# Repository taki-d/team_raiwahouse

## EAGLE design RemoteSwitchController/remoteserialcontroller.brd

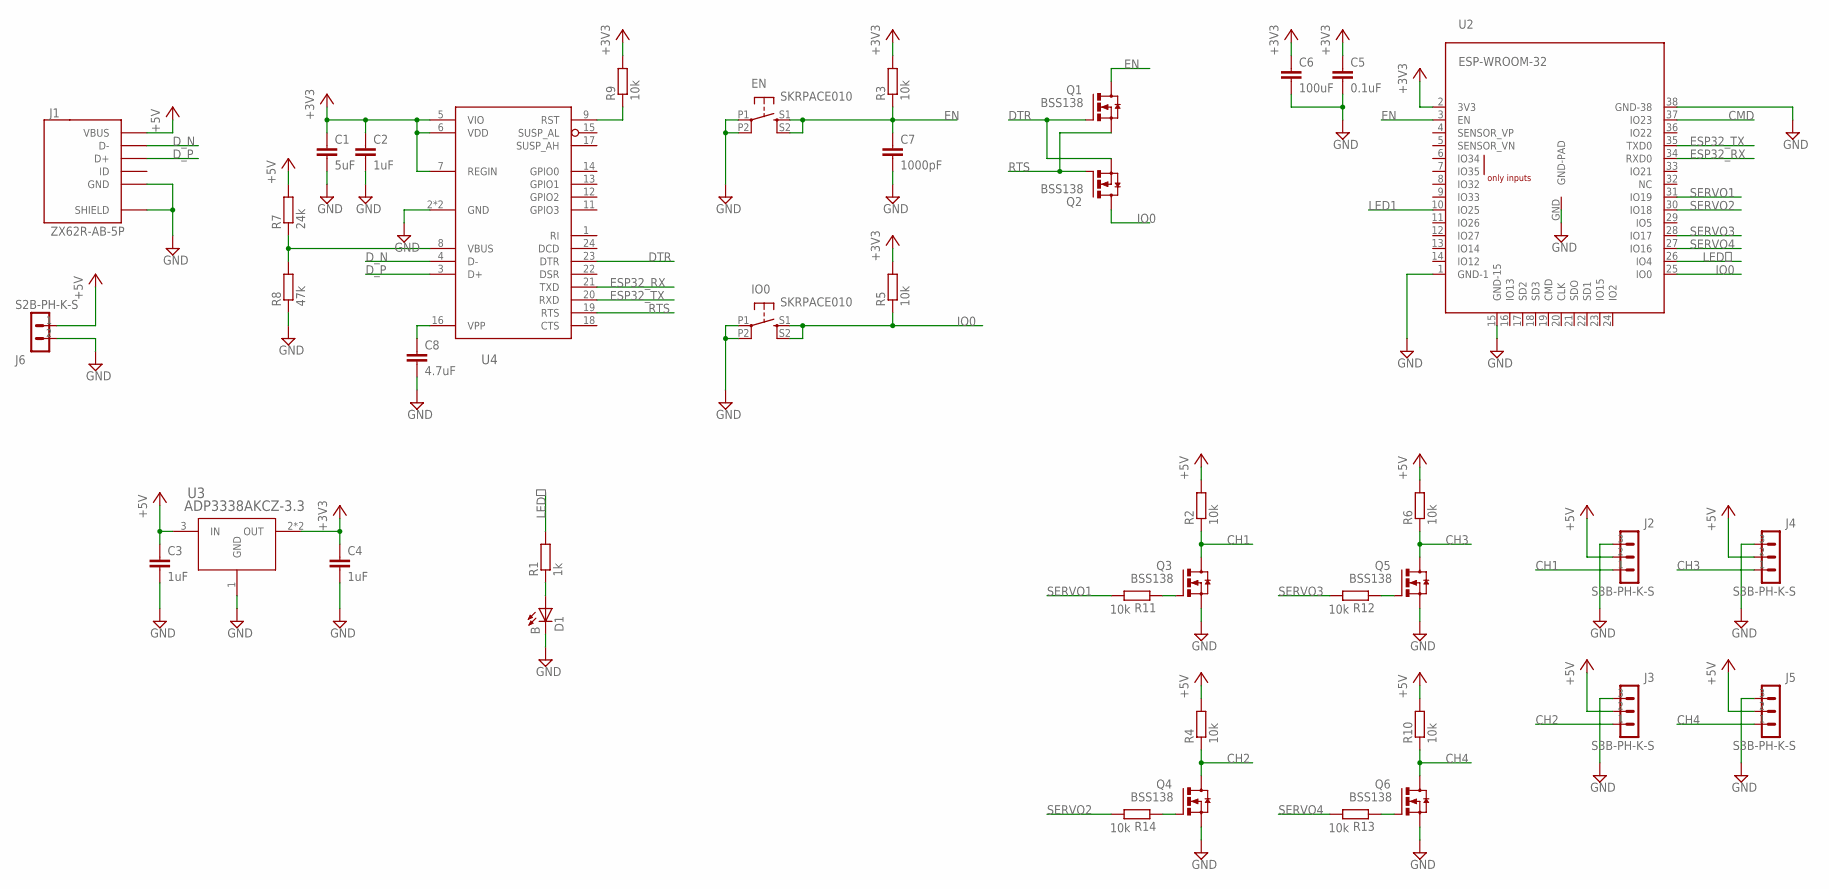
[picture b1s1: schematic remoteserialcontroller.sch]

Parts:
C1: 5uF; C0603
C2, C3, C4: 1uF; C0603
C5: 0.1uF; C0603
C6: 100uF; C1210
C7: 1000pF; C0603
C8: 4.7uF; C0603
D1: B; CHIPLED_0603
EN: SKRPACE010
IO0: SKRPACE010
J1: ZX62R-AB-5P; ZX62R-B-5PA
J2, J3, J4, J5: S3B-PH-K-S
J6: S2B-PH-K-S
Q1, Q2, Q3, Q4, Q5, Q6: BSS138; SOT23-N-MOSFET
R1: 1k; R0603
R2, R3, R4, R5, R6, R9, R10, R11, R12, R13, R14: 10k; R0603
R7: 24k; R0603
R8: 47k; R0603
U2: ESP-WROOM-32
U3: ADP3338AKCZ-3.3; SOT233
U4: CP2104; QFN24-SILABS

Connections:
+3V3: C1.1, C2.1, C4.1, C5.1, C6.1, R3.2, R5.2, R9.2, U2.2 (3V3), U3.2 (OUT), U3.4 (OUT), U4.5 (VIO), U4.6 (VDD), U4.7 (REGIN)
+5V: C3.1, J1.VCC (VBUS), J2.2, J3.2, J4.2, J5.2, J6.1, R2.2, R4.2, R6.2, R7.2, R10.2, U3.3 (IN)
CH1: J2.1, Q3.D, R2.1
CH2: J3.1, Q4.D, R4.1
CH3: J4.1, Q5.D, R6.1
CH4: J5.1, Q6.D, R10.1
CMD: U2.37 (IO23)
DTR: Q1.G, Q2.S, U4.23 (DTR)
D_N: J1.D-, U4.4 (D-)
D_P: J1.D+, U4.3 (D+)
EN: C7.1, EN.S1 (S), EN.S2 (S1), Q1.D, R3.1, U2.3 (EN)
ESP32_RX: U2.34 (RXD0), U4.21 (TXD)
ESP32_TX: U2.35 (TXD0), U4.20 (RXD)
GND: C1.2, C2.2, C3.2, C4.2, C5.2, C6.2, C7.2, C8.2, D1.C, EN.P1, EN.P2 (P1), IO0.P1, IO0.P2 (P1), J1.GND, J1.SHIELD@1 (SHIELD), J1.SHIELD@2 (SHIELD), J1.SHIELD@3 (SHIELD), J1.SHIELD@4 (SHIELD), J2.3, J3.3, J4.3, J5.3, J6.2, Q3.S, Q4.S, Q5.S, Q6.S, R8.1, U2.1 (GND-1), U2.15 (GND-15), U2.38 (GND-38), U2.GND (GND-PAD), U3.1 (GND), U4.2 (GND), U4.25 (GND)
IO0: IO0.S1 (S), IO0.S2 (S1), Q2.D, R5.1, U2.25 (IO0)
LED1: U2.10 (IO25)
LED１: R1.2, U2.26 (IO4)
unnamed: Q3.G, R11.1
unnamed: Q5.G, R12.1
unnamed: Q6.G, R13.1
unnamed: Q4.G, R14.1
unnamed: R9.1, U4.9 (RST)
unnamed: R7.1, R8.2, U4.8 (VBUS)
unnamed: C8.1, U4.16 (VPP)
unnamed: D1.A, R1.1
RTS: Q1.S, Q2.G, U4.19 (RTS)
SERVO1: R11.2, U2.31 (IO19)
SERVO2: R14.2, U2.30 (IO18)
SERVO3: R12.2, U2.28 (IO17)
SERVO4: R13.2, U2.27 (IO16)

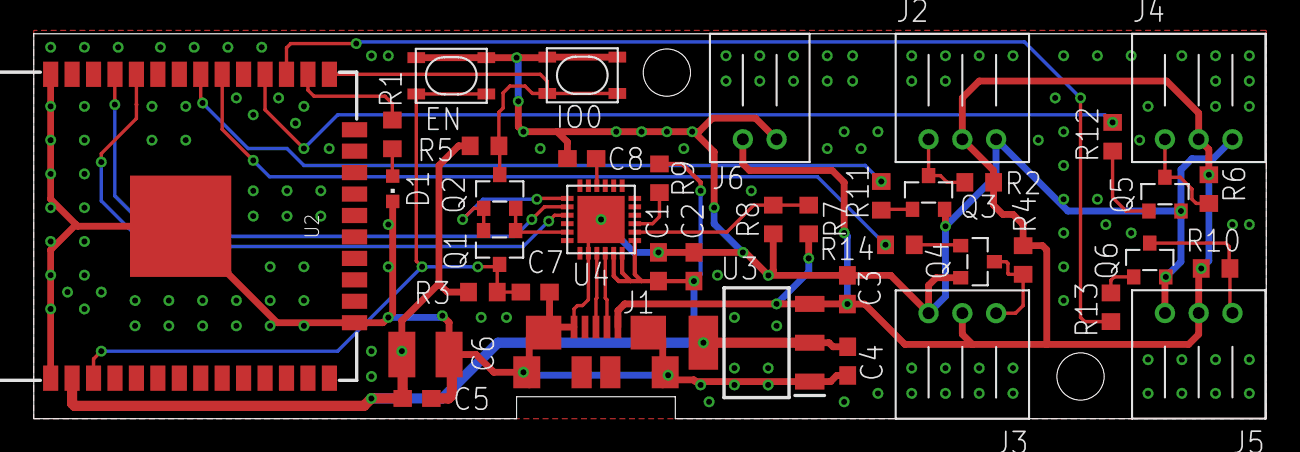
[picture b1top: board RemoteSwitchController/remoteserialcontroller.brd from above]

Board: 2 copper layers, 73.0 x 22.8 mm, 40 parts (0 on the bottom side), 28 nets.

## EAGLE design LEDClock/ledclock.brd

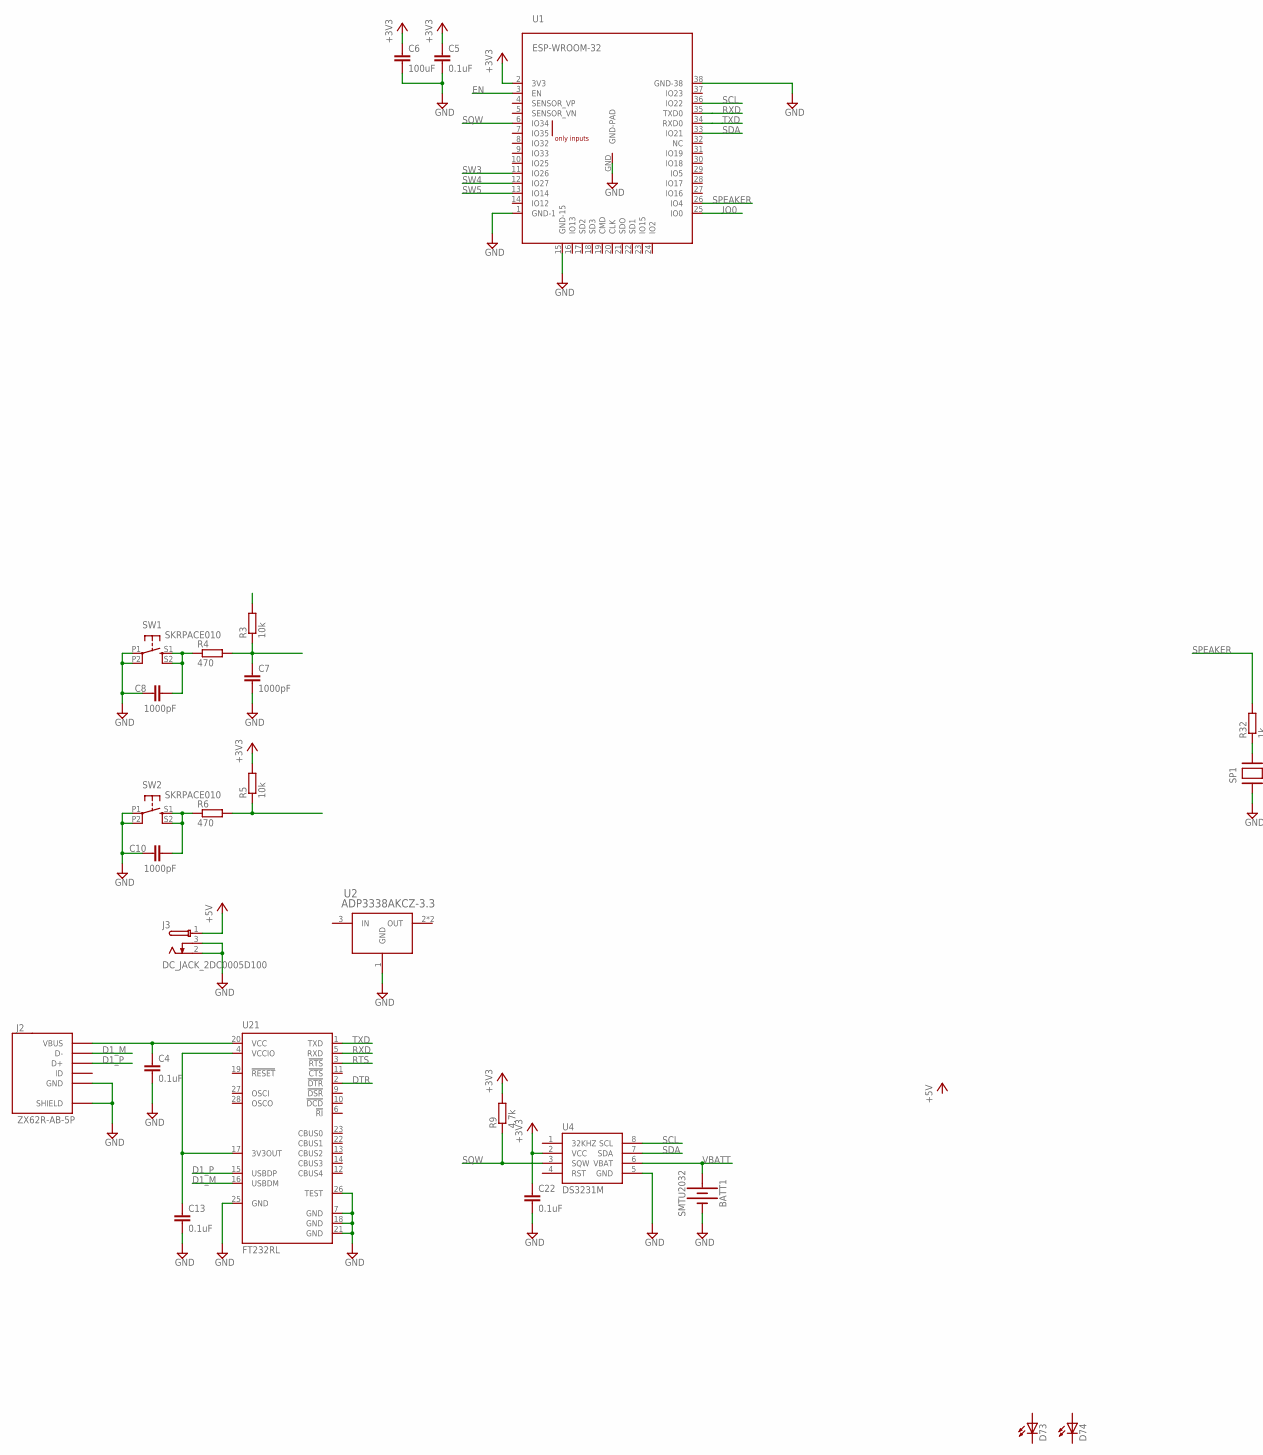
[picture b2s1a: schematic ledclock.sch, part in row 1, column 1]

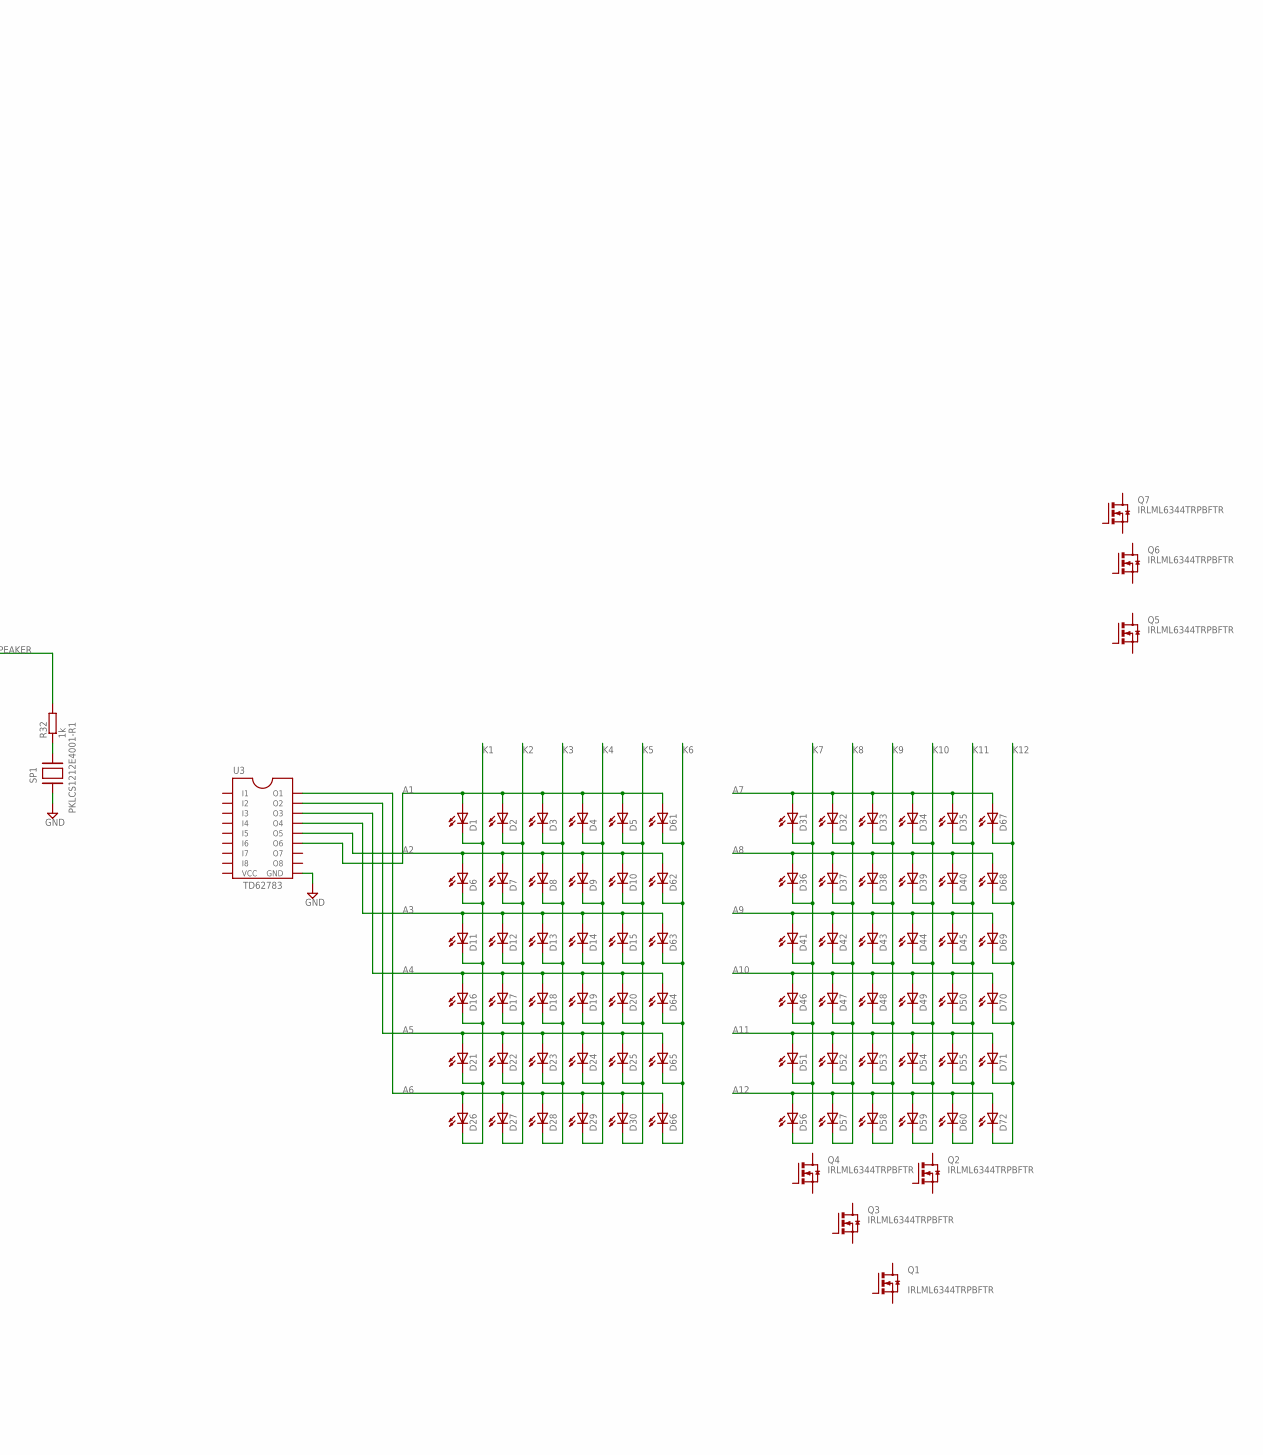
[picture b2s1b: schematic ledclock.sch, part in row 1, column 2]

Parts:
BATT1: SMTU2032
C4, C5, C13, C22: 0.1uF; C0603
C6: 100uF; C1210
C7, C8, C10: 1000pF; C0603
D1, D2, D3, D4, D5, D6, D7, D8, D9, D10, D11, D12, D13, D14, D15, D16, D17, D18, D19, D20, D21, D22, D23, D24, D25, D26, D27, D28, D29, D30, D31, D32, D33, D34, D35, D36, D37, D38, D39, D40, D41, D42, D43, D44, D45, D46, D47, D48, D49, D50, D51, D52, D53, D54, D55, D56, D57, D58, D59, D60, D61, D62, D63, D64, D65, D66, D67, D68, D69, D70, D71, D72, D73, D74: LED-H-0603; CHIPLED_0603-H
J2: ZX62R-AB-5P; ZX62R-B-5PA
J3: DC_JACK_2DC0005D100
Q1, Q2, Q3, Q4, Q5, Q6, Q7: IRLML6344TRPBFTR; SOT23-N-MOSFET
R3, R5: 10k; R0603
R4, R6: 470; R0603
R9: 4.7k; R0603
R32: 1k; R0603
SP1: PKLCS1212E4001-R1
SW1, SW2: SKRPACE010
U1: ESP-WROOM-32
U2: ADP3338AKCZ-3.3; SOT233
U3: TD62783; SOP18_TOSHIBA
U4: DS3231M; SO08
U21: FT232RL; SSOP28

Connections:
+3V3: C5.1, C6.1, C22.1, R3.2, R5.2, R9.2, U1.2 (3V3), U4.2 (VCC)
+5V: J3.1
A1: D1.A, D2.A, D3.A, D4.A, D5.A, D61.A, U3.13 (O6)
A2: D6.A, D7.A, D8.A, D9.A, D10.A, D62.A, U3.14 (O5)
A3: D11.A, D12.A, D13.A, D14.A, D15.A, D63.A, U3.15 (O4)
A4: D16.A, D17.A, D18.A, D19.A, D20.A, D64.A, U3.16 (O3)
A5: D21.A, D22.A, D23.A, D24.A, D25.A, D65.A, U3.17 (O2)
A6: D26.A, D27.A, D28.A, D29.A, D30.A, D66.A, U3.18 (O1)
A7: D31.A, D32.A, D33.A, D34.A, D35.A, D67.A
A8: D36.A, D37.A, D38.A, D39.A, D40.A, D68.A
A9: D41.A, D42.A, D43.A, D44.A, D45.A, D69.A
A10: D46.A, D47.A, D48.A, D49.A, D50.A, D70.A
A11: D51.A, D52.A, D53.A, D54.A, D55.A, D71.A
A12: D56.A, D57.A, D58.A, D59.A, D60.A, D72.A
D1_M: J2.D-, U21.16 (USBDM)
D1_P: J2.D+, U21.15 (USBDP)
DTR: U21.2 (!DTR)
EN: C7.1, R3.1, R4.2, U1.3 (EN)
GND: BATT1.N (-), C4.2, C5.2, C6.2, C7.2, C8.1, C10.1, C13.2, C22.2, J2.GND, J2.SHIELD@1 (SHIELD), J2.SHIELD@2 (SHIELD), J2.SHIELD@3 (SHIELD), J2.SHIELD@4 (SHIELD), J3.2, J3.3, SP1.2, SW1.P1, SW1.P2 (P1), SW2.P1, SW2.P2 (P1), U1.1 (GND-1), U1.15 (GND-15), U1.38 (GND-38), U1.GND (GND-PAD), U2.1 (GND), U3.10 (GND), U4.5 (GND), U21.7 (GND), U21.18 (GND), U21.21 (GND), U21.25 (GND), U21.26 (TEST)
IO0: R5.1, R6.2, U1.25 (IO0)
K1: D1.C, D6.C, D11.C, D16.C, D21.C, D26.C
K2: D2.C, D7.C, D12.C, D17.C, D22.C, D27.C
K3: D3.C, D8.C, D13.C, D18.C, D23.C, D28.C
K4: D4.C, D9.C, D14.C, D19.C, D24.C, D29.C
K5: D5.C, D10.C, D15.C, D20.C, D25.C, D30.C
K6: D61.C, D62.C, D63.C, D64.C, D65.C, D66.C
K7: D31.C, D36.C, D41.C, D46.C, D51.C, D56.C
K8: D32.C, D37.C, D42.C, D47.C, D52.C, D57.C
K9: D33.C, D38.C, D43.C, D48.C, D53.C, D58.C
K10: D34.C, D39.C, D44.C, D49.C, D54.C, D59.C
K11: D35.C, D40.C, D45.C, D50.C, D55.C, D60.C
K12: D67.C, D68.C, D69.C, D70.C, D71.C, D72.C
unnamed: C8.2, R4.1, SW1.S1 (S), SW1.S2 (S1)
unnamed: C10.2, R6.1, SW2.S1 (S), SW2.S2 (S1)
unnamed: R32.1, SP1.1
unnamed: C13.1, U21.4 (VCCIO), U21.17 (3V3OUT)
unnamed: C4.1, J2.VCC (VBUS), U21.20 (VCC)
RTS: U21.3 (!RTS)
RXD: U1.35 (TXD0), U21.5 (RXD)
SCL: U1.36 (IO22), U4.8 (SCL)
SDA: U1.33 (IO21), U4.7 (SDA)
SPEAKER: R32.2, U1.26 (IO4)
SQW: R9.1, U1.6 (IO34), U4.3 (SQW)
SW3: U1.11 (IO26)
SW4: U1.12 (IO27)
SW5: U1.13 (IO14)
TXD: U1.34 (RXD0), U21.1 (TXD)
VBATT: BATT1.P (+), U4.6 (VBAT)

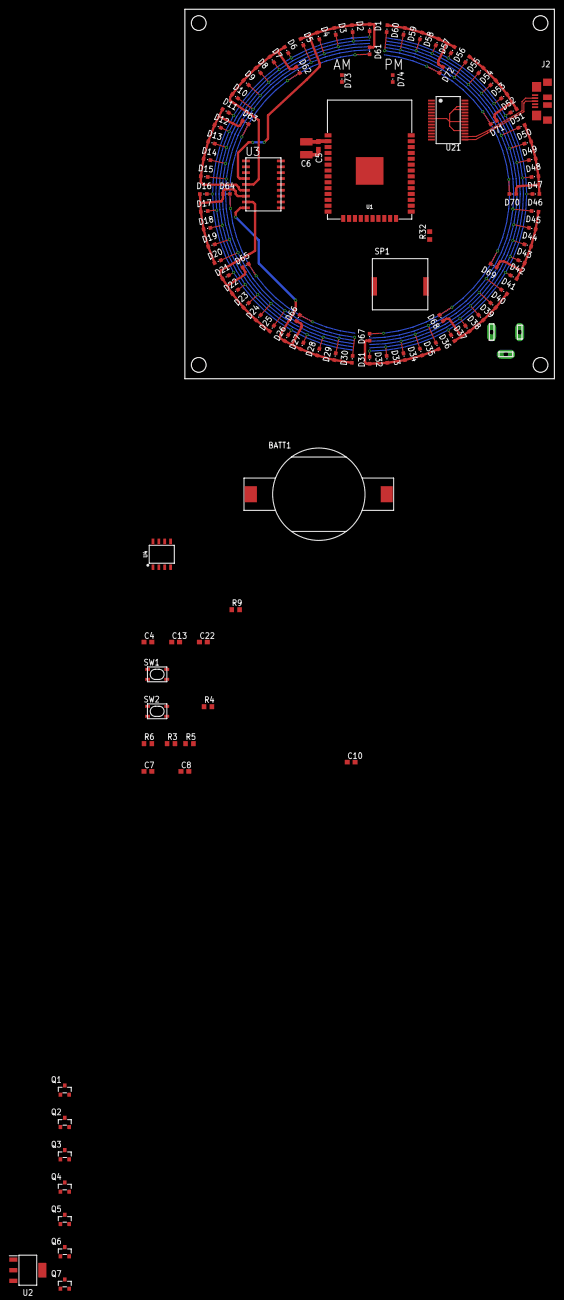
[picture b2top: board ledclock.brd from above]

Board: 2 copper layers, 80.0 x 80.0 mm, 106 parts (1 on the bottom side), 42 nets.

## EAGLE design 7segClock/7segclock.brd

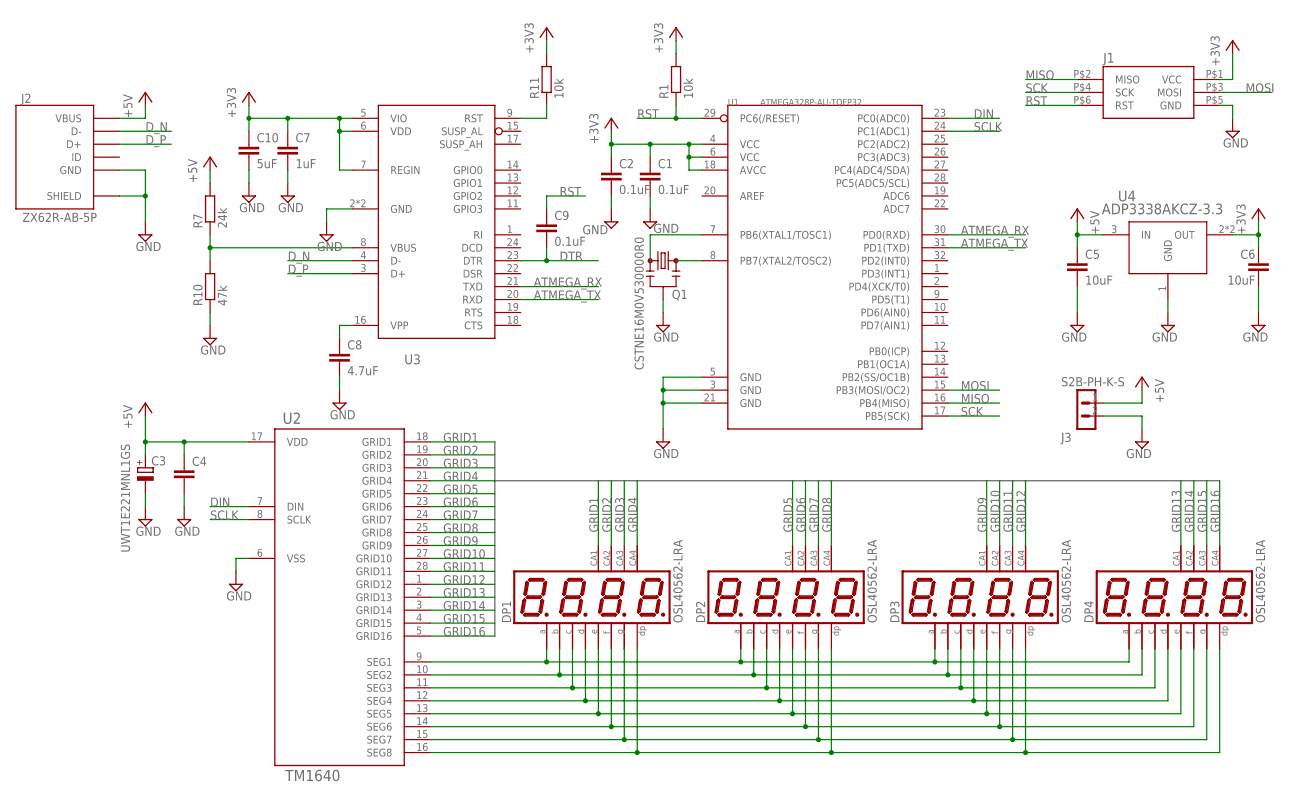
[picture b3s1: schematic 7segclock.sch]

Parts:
C1, C2, C9: 0.1uF; C0603
C3: UWT1E221MNL1GS; NICHICON-ALMINUM-CAPACITOR-8MM
C4: C-EUC0603; C0603
C5, C6: 10uF; C0603
C7: 1uF; C0603
C8: 4.7uF; C0603
C10: 5uF; C0603
DP1, DP2, DP3, DP4: OSL40562-LRA
J1: ICSP; PIN_HEADER_MALE_2X03_06P
J2: ZX62R-AB-5P; ZX62R-B-5PA
J3: S2B-PH-K-S
Q1: CSTNE16M0V530000R0
R1, R11: 10k; R0603
R7: 24k; R0603
R10: 47k; R0603
U1: ATMEGA328P-AU-TQFP32; TQFP32-0.8-7X7MM
U2: TM1640; SOP28-TITANMICROELECTRONICS
U3: CP2104; QFN24-SILABS
U4: ADP3338AKCZ-3.3; SOT233

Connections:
+3V3: C1.1, C2.1, C6.1, C7.1, C10.1, J1.P$1 (VCC), R1.2, R11.2, U1.4 (VCC), U1.6 (VCC), U1.18 (AVCC), U3.5 (VIO), U3.6 (VDD), U3.7 (REGIN), U4.2 (OUT), U4.4 (OUT)
+5V: C3.POS (+), C4.1, C5.1, J2.VCC (VBUS), J3.1, R7.2, U2.17 (VDD), U4.3 (IN)
ATMEGA_RX: U1.30 (PD0(RXD)), U3.21 (TXD)
ATMEGA_TX: U1.31 (PD1(TXD)), U3.20 (RXD)
DIN: U1.23 (PC0(ADC0)), U2.7 (DIN)
DTR: C9.2, U3.23 (DTR)
D_N: J2.D-, U3.4 (D-)
D_P: J2.D+, U3.3 (D+)
GND: C1.2, C2.2, C3.NEG (-), C4.2, C5.2, C6.2, C7.2, C8.2, C10.2, J1.P$5 (GND), J2.GND, J2.SHIELD@1 (SHIELD), J2.SHIELD@2 (SHIELD), J2.SHIELD@3 (SHIELD), J2.SHIELD@4 (SHIELD), J3.2, Q1.2, R10.1, U1.3 (GND), U1.5 (GND), U1.21 (GND), U2.6 (VSS), U3.2 (GND), U3.25 (GND), U4.1 (GND)
GRID1: DP1.DIG1 (CA), U2.18 (GRID1)
GRID2: DP1.DIG2 (CA), U2.19 (GRID2)
GRID3: DP1.DIG3 (CA), U2.20 (GRID3)
GRID4: DP1.DIG4 (CA), U2.21 (GRID4)
GRID5: DP2.DIG1 (CA), U2.22 (GRID5)
GRID6: DP2.DIG2 (CA), U2.23 (GRID6)
GRID7: DP2.DIG3 (CA), U2.24 (GRID7)
GRID8: DP2.DIG4 (CA), U2.25 (GRID8)
GRID9: DP3.DIG1 (CA), U2.26 (GRID9)
GRID10: DP3.DIG2 (CA), U2.27 (GRID10)
GRID11: DP3.DIG3 (CA), U2.28 (GRID11)
GRID12: DP3.DIG4 (CA), U2.1 (GRID12)
GRID13: DP4.DIG1 (CA), U2.2 (GRID13)
GRID14: DP4.DIG2 (CA), U2.3 (GRID14)
GRID15: DP4.DIG3 (CA), U2.4 (GRID15)
GRID16: DP4.DIG4 (CA), U2.5 (GRID16)
MISO: J1.P$2 (MISO), U1.16 (PB4(MISO))
MOSI: J1.P$3 (MOSI), U1.15 (PB3(MOSI/OC2))
unnamed: DP1.A, DP2.A, DP3.A, DP4.A, U2.9 (SEG1)
unnamed: DP1.B, DP2.B, DP3.B, DP4.B, U2.10 (SEG2)
unnamed: DP1.C, DP2.C, DP3.C, DP4.C, U2.11 (SEG3)
unnamed: DP1.D, DP2.D, DP3.D, DP4.D, U2.12 (SEG4)
unnamed: DP1.E, DP2.E, DP3.E, DP4.E, U2.13 (SEG5)
unnamed: DP1.F, DP2.F, DP3.F, DP4.F, U2.14 (SEG6)
unnamed: DP1.G, DP2.G, DP3.G, DP4.G, U2.15 (SEG7)
unnamed: DP1.DP, DP2.DP, DP3.DP, DP4.DP, U2.16 (SEG8)
unnamed: C8.1, U3.16 (VPP)
unnamed: Q1.3, U1.8 (PB7(XTAL2/TOSC2))
unnamed: Q1.1, U1.7 (PB6(XTAL1/TOSC1))
unnamed: R7.1, R10.2, U3.8 (VBUS)
unnamed: R11.1, U3.9 (RST)
RST: C9.1, J1.P$6 (RST), R1.1, U1.29 (PC6(/RESET))
SCK: J1.P$4 (SCK), U1.17 (PB5(SCK))
SCLK: U1.24 (PC1(ADC1)), U2.8 (SCLK)

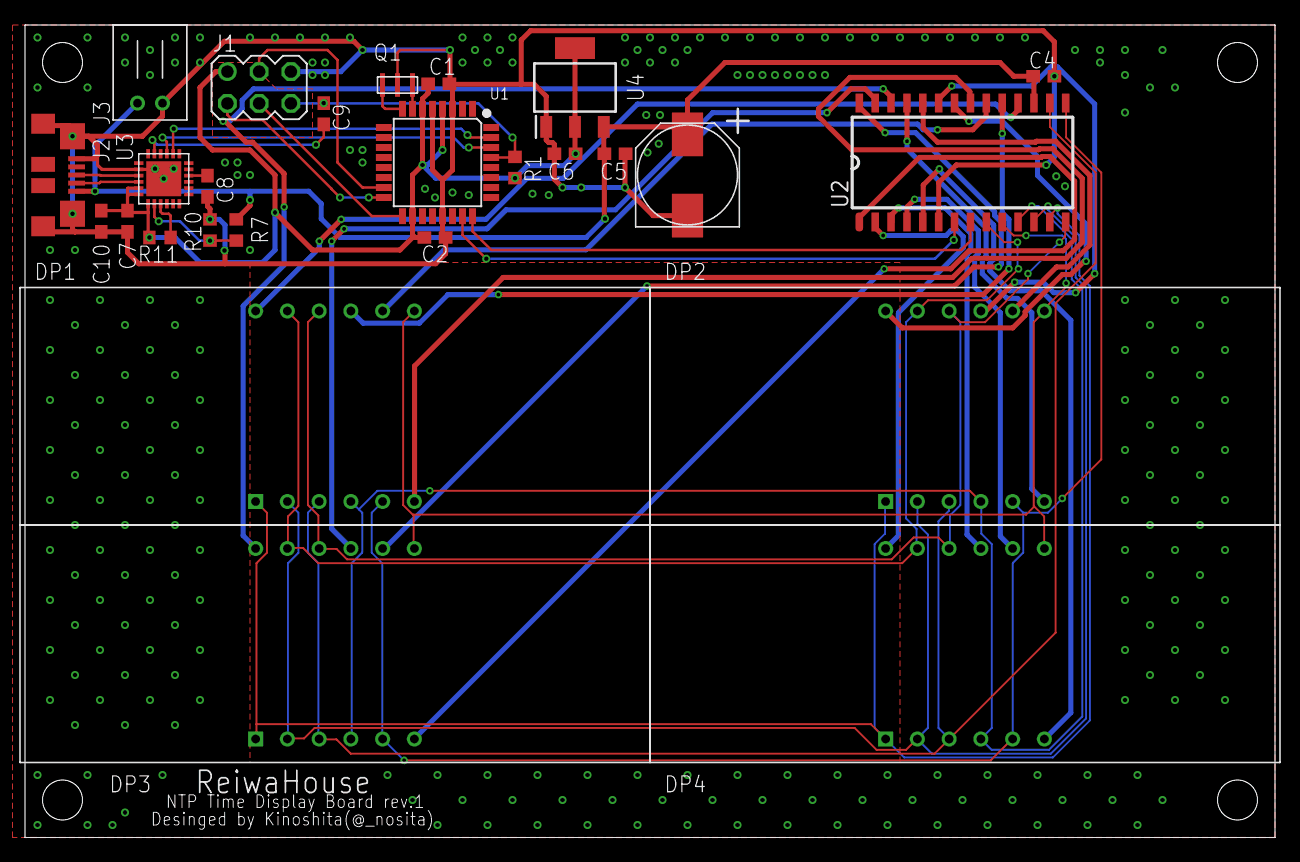
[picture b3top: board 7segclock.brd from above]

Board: 2 copper layers, 100.0 x 65.0 mm, 26 parts (0 on the bottom side), 43 nets.

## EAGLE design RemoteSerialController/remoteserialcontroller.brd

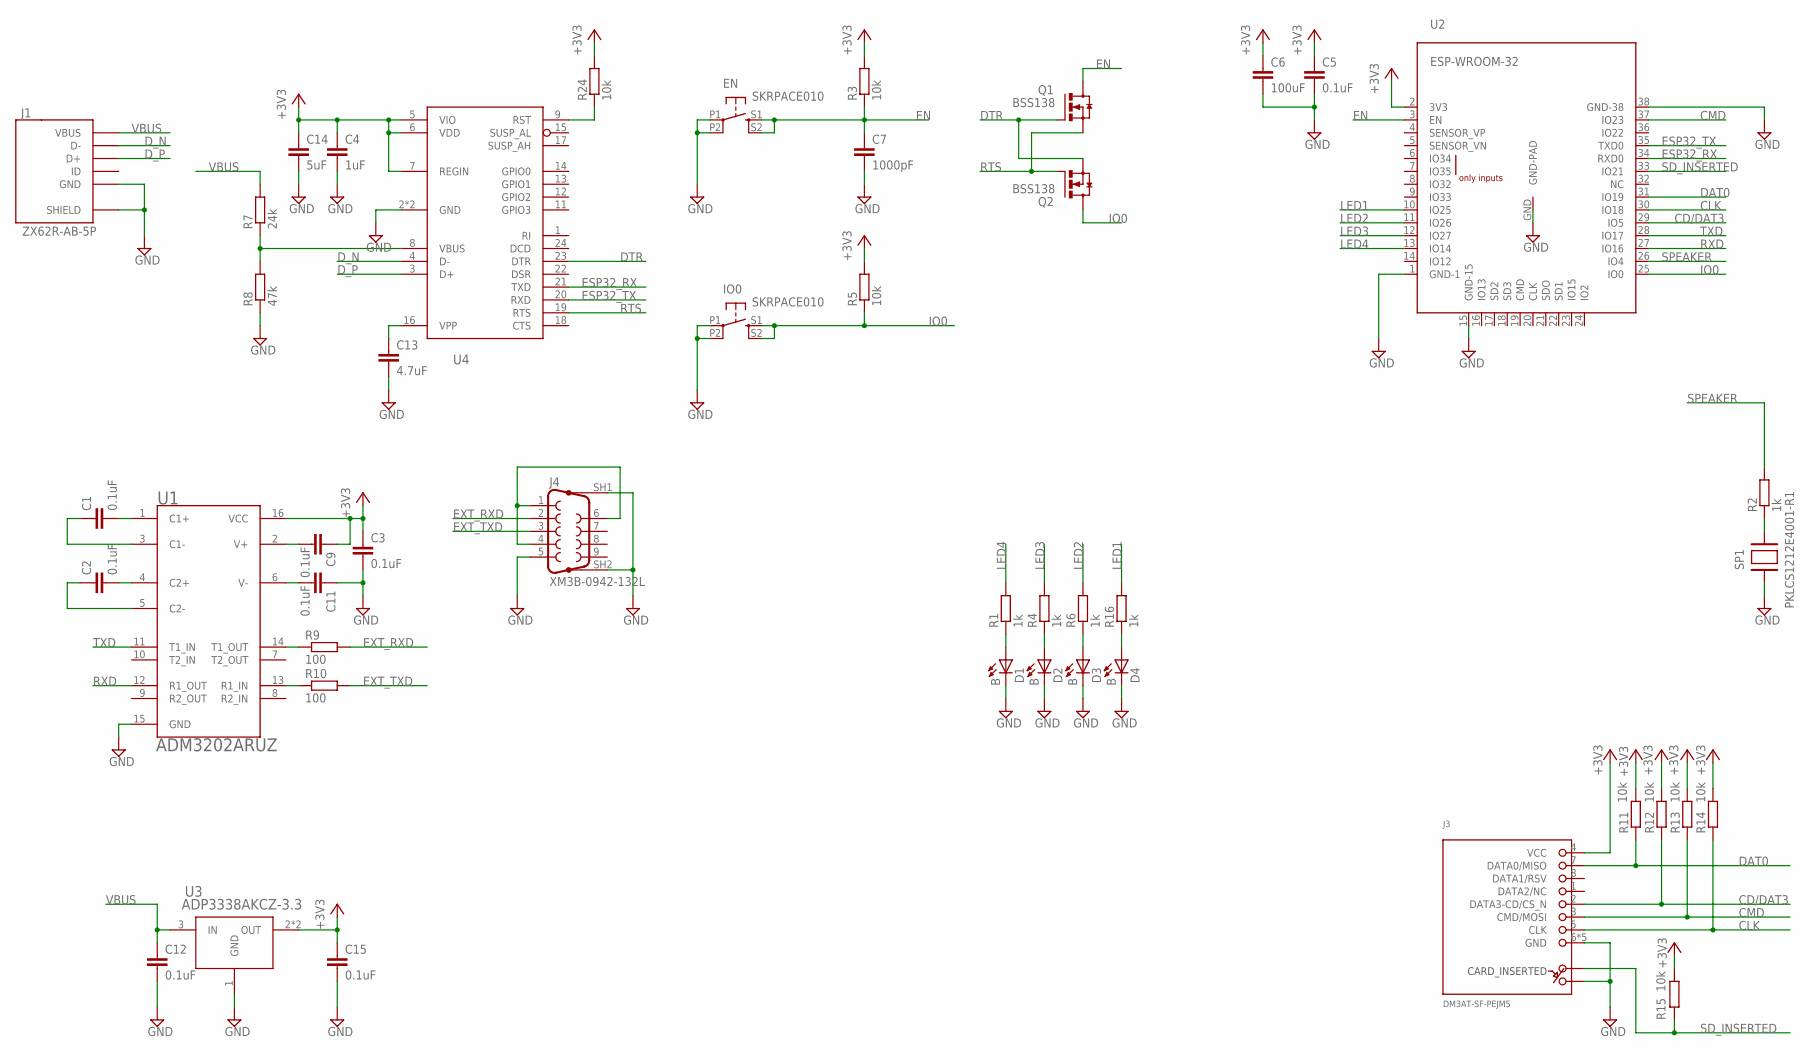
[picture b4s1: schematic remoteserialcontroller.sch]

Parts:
C1, C2, C3, C5, C9, C11, C12, C15: 0.1uF; C0603
C4: 1uF; C0603
C6: 100uF; C1210
C7: 1000pF; C0603
C13: 4.7uF; C0603
C14: 5uF; C0603
D1, D2, D3, D4: B; CHIPLED_0603
EN: SKRPACE010
IO0: SKRPACE010
J1: ZX62R-AB-5P; ZX62R-B-5PA
J3: DM3AT-SF-PEJM5
J4: XM3B-0942-132L
Q1, Q2: BSS138; SOT23-N-MOSFET
R1, R2, R4, R6, R16: 1k; R0603
R3, R5, R11, R12, R13, R14, R15, R24: 10k; R0603
R7: 24k; R0603
R8: 47k; R0603
R9, R10: 100; R0603
SP1: PKLCS1212E4001-R1
U1: ADM3202ARUZ; TSSOP16-AD
U2: ESP-WROOM-32
U3: ADP3338AKCZ-3.3; SOT233
U4: CP2104; QFN24-SILABS

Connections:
+3V3: C3.1, C4.1, C5.1, C6.1, C9.1, C14.1, C15.1, J3.4 (VCC), R3.2, R5.2, R11.2, R12.2, R13.2, R14.2, R15.2, R24.2, U1.16 (VCC), U2.2 (3V3), U3.2 (OUT), U3.4 (OUT), U4.5 (VIO), U4.6 (VDD), U4.7 (REGIN)
CD/DAT3: J3.2 (DATA3-CD/CS_N), R12.1, U2.29 (IO5)
CLK: J3.5 (CLK), R14.1, U2.30 (IO18)
CMD: J3.3 (CMD/MOSI), R13.1, U2.37 (IO23)
DAT0: J3.7 (DATA0/MISO), R11.1, U2.31 (IO19)
DTR: Q1.G, Q2.S, U4.23 (DTR)
D_N: J1.D-, U4.4 (D-)
D_P: J1.D+, U4.3 (D+)
EN: C7.1, EN.S1 (S), EN.S2 (S1), Q1.D, R3.1, U2.3 (EN)
ESP32_RX: U2.34 (RXD0), U4.21 (TXD)
ESP32_TX: U2.35 (TXD0), U4.20 (RXD)
EXT_RXD: J4.2, R9.2
EXT_TXD: J4.3, R10.2
GND: C3.2, C4.2, C5.2, C6.2, C7.2, C11.1, C12.2, C13.2, C14.2, C15.2, D1.C, D2.C, D3.C, D4.C, EN.P1, EN.P2 (P1), IO0.P1, IO0.P2 (P1), J1.GND, J1.SHIELD@1 (SHIELD), J1.SHIELD@2 (SHIELD), J1.SHIELD@3 (SHIELD), J1.SHIELD@4 (SHIELD), J3.6 (GND), J3.B, J3.MOUNT0 (GND), J3.MOUNT1 (GND), J3.MOUNT2 (GND), J3.MOUNT3 (GND), J4.5, J4.SH1 (G1), J4.SH2 (G2), R8.1, SP1.2, U1.15 (GND), U2.1 (GND-1), U2.15 (GND-15), U2.38 (GND-38), U2.GND (GND-PAD), U3.1 (GND), U4.2 (GND), U4.25 (GND)
IO0: IO0.S1 (S), IO0.S2 (S1), Q2.D, R5.1, U2.25 (IO0)
LED1: R16.2, U2.10 (IO25)
LED2: R6.2, U2.11 (IO26)
LED3: R4.2, U2.12 (IO27)
LED4: R1.2, U2.13 (IO14)
unnamed: J4.1, J4.4, J4.6
unnamed: R9.1, U1.14 (T1_OUT)
unnamed: R10.1, U1.13 (R1_IN)
unnamed: D2.A, R4.1
unnamed: D3.A, R6.1
unnamed: D4.A, R16.1
unnamed: R24.1, U4.9 (RST)
unnamed: R7.1, R8.2, U4.8 (VBUS)
unnamed: C13.1, U4.16 (VPP)
unnamed: C1.2, U1.1 (C1+)
unnamed: C1.1, U1.3 (C1-)
unnamed: C2.2, U1.4 (C2+)
unnamed: C2.1, U1.5 (C2-)
unnamed: C9.2, U1.2 (V+)
unnamed: C11.2, U1.6 (V-)
unnamed: R2.1, SP1.1
unnamed: D1.A, R1.1
RTS: Q1.S, Q2.G, U4.19 (RTS)
RXD: U1.12 (R1_OUT), U2.27 (IO16)
SD_INSERTED: J3.A, R15.1, U2.33 (IO21)
SPEAKER: R2.2, U2.26 (IO4)
TXD: U1.11 (T1_IN), U2.28 (IO17)
VBUS: C12.1, J1.VCC (VBUS), R7.2, U3.3 (IN)

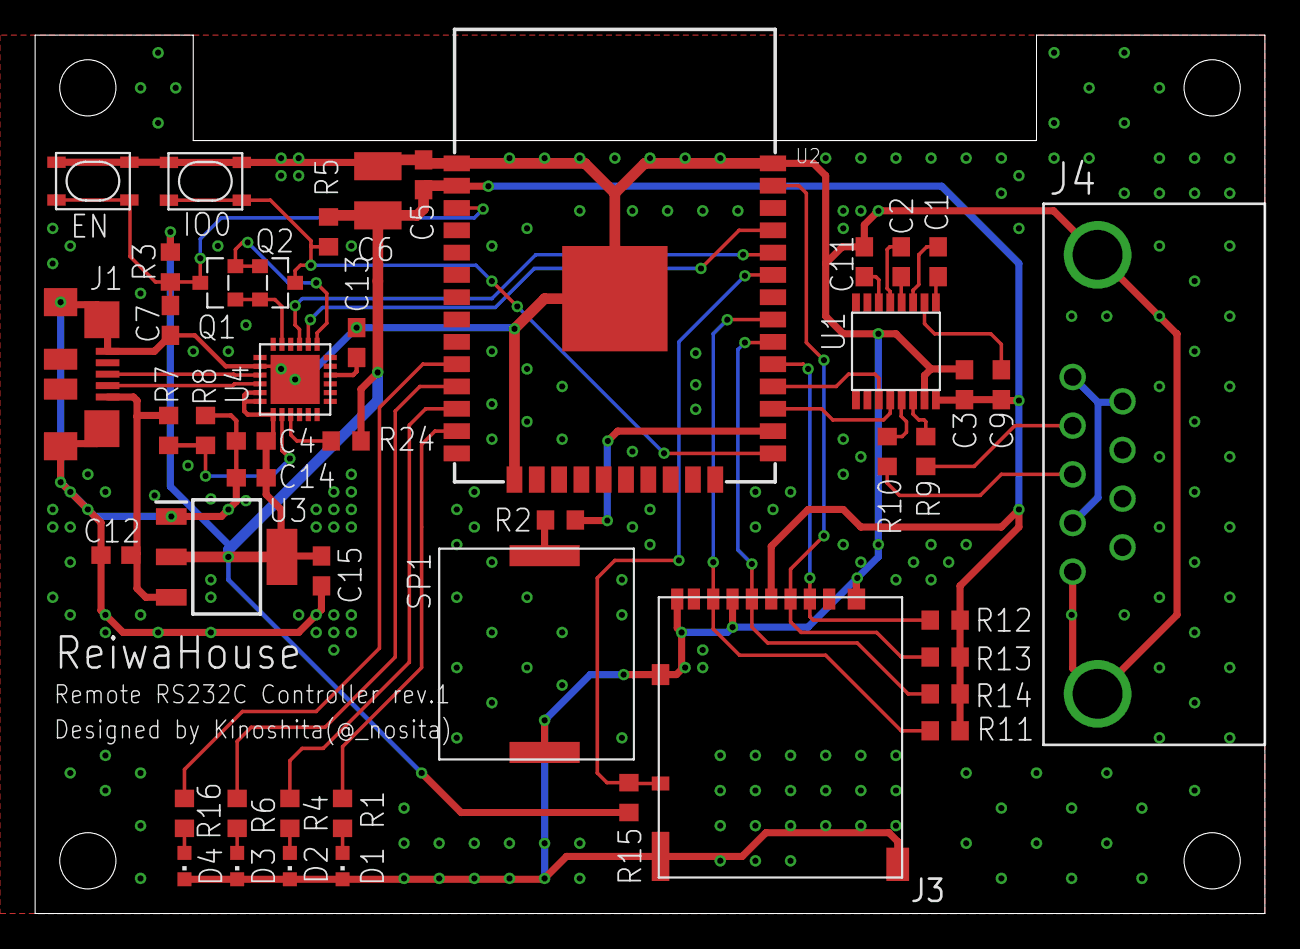
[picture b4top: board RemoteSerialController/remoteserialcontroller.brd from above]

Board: 2 copper layers, 70.0 x 50.0 mm, 46 parts (0 on the bottom side), 42 nets.

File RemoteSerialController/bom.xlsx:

Column1 | Column2 | Column3 | Column4 | 列1
Part | Value | Device | Package | Description
C1 | 0.1uF | C-EUC0603 | C0603 | CAPACITOR, European symbol
C2 | 0.1uF | C-EUC0603 | C0603 | CAPACITOR, European symbol
C3 | 0.1uF | C-EUC0603 | C0603 | CAPACITOR, European symbol
C4 | 1uF | C-EUC0603 | C0603 | CAPACITOR, European symbol
C5 | 0.1uF | C-EUC0603 | C0603 | CAPACITOR, European symbol
C6 | 100uF | C-EUC1210 | C1210 | CAPACITOR, European symbol
C7 | 1000pF | C-EUC0603 | C0603 | CAPACITOR, European symbol
C9 | 0.1uF | C-EUC0603 | C0603 | CAPACITOR, European symbol
C11 | 0.1uF | C-EUC0603 | C0603 | CAPACITOR, European symbol
C12 | 0.1uF | C-EUC0603 | C0603 | CAPACITOR, European symbol
C13 | 4.7uF | C-EUC0603 | C0603 | CAPACITOR, European symbol
C14 | 5uF | C-EUC0603 | C0603 | CAPACITOR, European symbol
C15 | 0.1uF | C-EUC0603 | C0603 | CAPACITOR, European symbol
D1 | B | LEDCHIPLED_0603 | CHIPLED_0603 | LED
D2 | B | LEDCHIPLED_0603 | CHIPLED_0603 | LED
D3 | B | LEDCHIPLED_0603 | CHIPLED_0603 | LED
D4 | B | LEDCHIPLED_0603 | CHIPLED_0603 | LED
EN | SKRPACE010 | SKRPACE010 | SKRPACE010
IO0 | SKRPACE010 | SKRPACE010 | SKRPACE010
J1 | ZX62R-AB-5P | ZX62R-AB-5P | ZX62R-B-5PA
J3 | DM3AT-SF-PEJM5 | DM3AT-SF-PEJM5 | DM3AT-SF-PEJM5 | CONN MICRO SD R/A PUSH-PUSH SMD
J4 | XM3B-0942-132L | XM3B-0942-132L | XM3B-0942-132L
Q1 | BSS138 | BSS138 | SOT23-N-MOSFET
Q2 | BSS138 | BSS138 | SOT23-N-MOSFET
R1 | 1k | R-EU_R0603 | R0603 | RESISTOR, European symbol
R2 | 1k | R-EU_R0603 | R0603 | RESISTOR, European symbol
R3 | 10k | R-EU_R0603 | R0603 | RESISTOR, European symbol
R4 | 1k | R-EU_R0603 | R0603 | RESISTOR, European symbol
R5 | 10k | R-EU_R0603 | R0603 | RESISTOR, European symbol
R6 | 1k | R-EU_R0603 | R0603 | RESISTOR, European symbol
R7 | 24k | R-EU_R0603 | R0603 | RESISTOR, European symbol
R8 | 47k | R-EU_R0603 | R0603 | RESISTOR, European symbol
R9 | 100 | R-EU_R0603 | R0603 | RESISTOR, European symbol
R10 | 100 | R-EU_R0603 | R0603 | RESISTOR, European symbol
R11 | 10k | R-EU_R0603 | R0603 | RESISTOR, European symbol
R12 | 10k | R-EU_R0603 | R0603 | RESISTOR, European symbol
R13 | 10k | R-EU_R0603 | R0603 | RESISTOR, European symbol
R14 | 10k | R-EU_R0603 | R0603 | RESISTOR, European symbol
R15 | 10k | R-EU_R0603 | R0603 | RESISTOR, European symbol
R16 | 1k | R-EU_R0603 | R0603 | RESISTOR, European symbol
R24 | 10k | R-EU_R0603 | R0603 | RESISTOR, European symbol
SP1 | PKLCS1212E4001-R1 | PKLCS1212E4001-R1 | PKLCS1212E4001-R1
U1 | ADM3202ARUZ | ADM3202ARUZ | TSSOP16-AD
U2 | ESP-WROOM-32 | ESP-WROOM-32 | ESP-WROOM-32
U3 | ADP3338AKCZ-3.3 | ADP3338AKCZ-3.3 | SOT233
U4 | CP2104 | CP2104 | QFN24-SILABS

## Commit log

2019-10-30 [add]initialize project
2019-12-02 [add] temporrary
2019-12-02 [fin]finish design
2019-12-19 [add]add all
2019-12-20 [add]add 7seg clokc before autoroute
2019-12-20 [add]add gerver output of 7seg clokc
2020-01-15 [update]update schematic and add BOM
